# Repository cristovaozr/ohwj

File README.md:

# OHWJ - Open hardware Joystick

Open hardware joystick - OHWJ (pronounces Oh-Jay) - is the first project where I am attempting to build a hardware with basic firmware for the controller setup.

## CPU

The CPU is an STM32F030C6 microcontroller with the following hardware enabled

* LQFP48 48 pin, 32K FLASH and 4K of SRAM, 7mm x 7mm size;
* 48MHz with internal 8MHz oscillator external 8MHz XTAL;
* Full 16-bit input port for buttons with internal pull-up resistors enabled;
  * No additional hardware for buttons necessary! If LOW then button is pressed;
* Four 12bit ADC channels for analog inputs;
  * 1kHz default frequency sampling for the buttons and ADC provided by internal timer (TIM14);
* SPI Full-duplex SPI for data transfer;
* Dedicated ST-Link pins available for debugging and flashing purposes.

Optional stuff:
* USART
* I2C
* GPIO:
  * Up to 8 GPIO available if external XTAL is not available;
  * Up to 6 GPIO available if external XTAL is available.

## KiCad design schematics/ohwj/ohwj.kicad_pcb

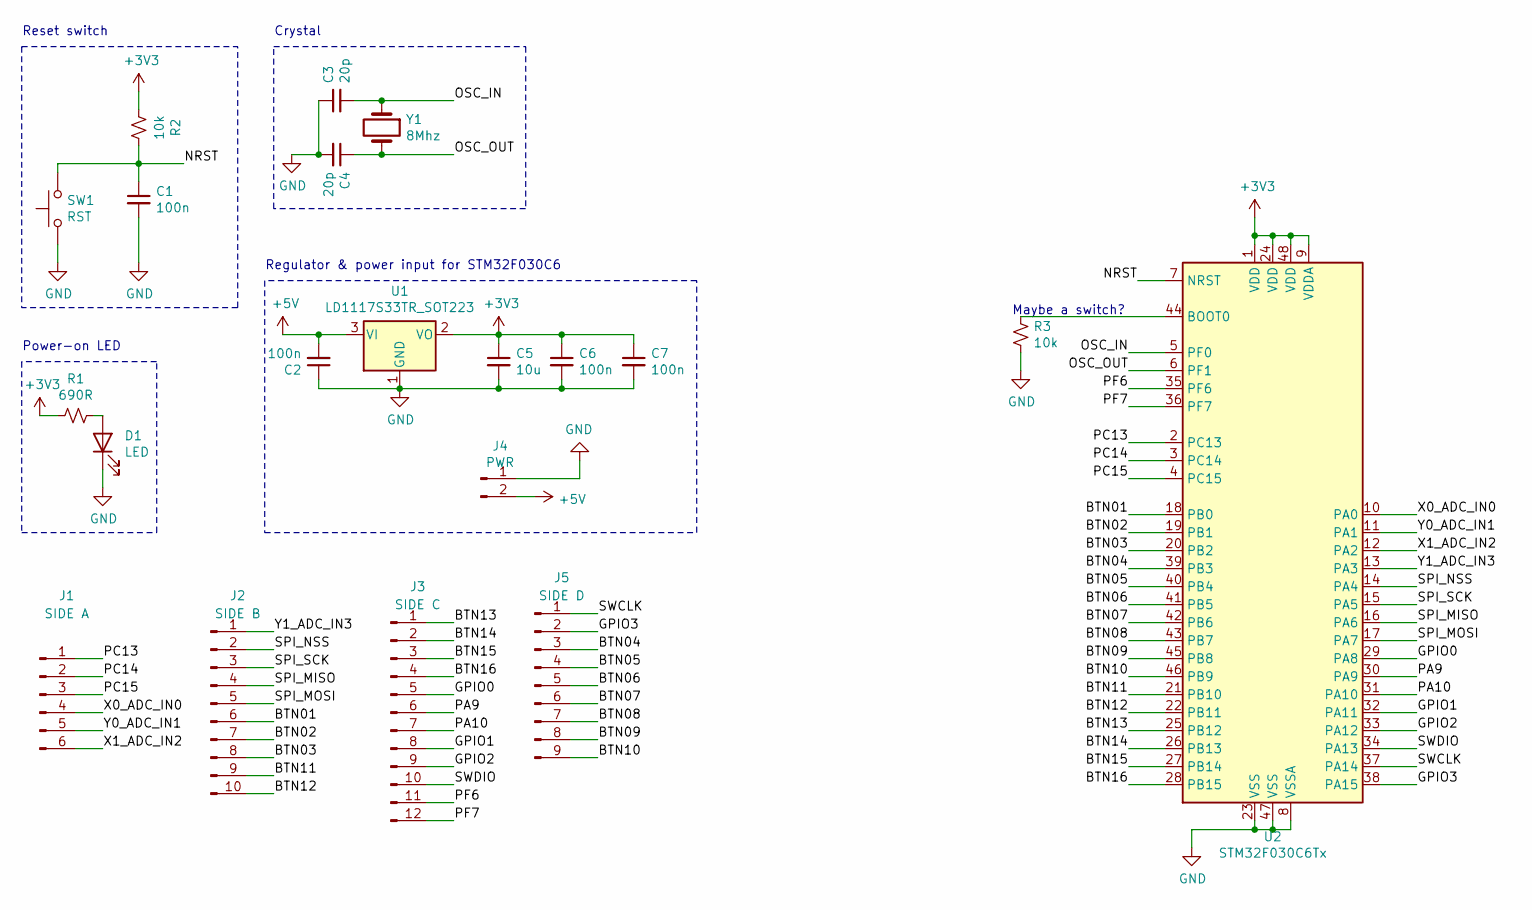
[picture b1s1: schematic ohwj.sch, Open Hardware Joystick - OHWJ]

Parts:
C1, C2, C6, C7: 100n; C_0603_1608Metric
C3, C4: 20p; C_0603_1608Metric
C5: 10u; C_0603_1608Metric
D1: LED; LED_0603_1608Metric
J1: SIDE A; PinHeader_1x06_P2.54mm_Vertical
J2: SIDE B; PinHeader_1x10_P2.54mm_Vertical
J3: SIDE C; PinHeader_1x12_P2.54mm_Vertical
J4: PWR; PinHeader_1x02_P2.54mm_Vertical
J5: SIDE D; PinHeader_1x09_P2.54mm_Vertical
R1: 690R; R_0603_1608Metric
R2, R3: 10k; R_0603_1608Metric
SW1: RST; SW_PUSH_6mm_H4.3mm
U1: LD1117S33TR_SOT223; SOT-223-3_TabPin2
U2: STM32F030C6Tx; LQFP-48_7x7mm_P0.5mm
Y1: 8Mhz; Crystal_HC49-4H_Vertical

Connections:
+3V3: C5.1, C6.1, C7.1, R1.1, R2.1, U1.2 (VO), U2.1 (VDD), U2.9 (VDDA), U2.24 (VDD), U2.48 (VDD)
+5V: C2.2, J4.2, U1.3 (VI)
/BTN01: J2.6, U2.18 (PB0)
/BTN02: J2.7, U2.19 (PB1)
/BTN03: J2.8, U2.20 (PB2)
/BTN04: J5.3, U2.39 (PB3)
/BTN05: J5.4, U2.40 (PB4)
/BTN06: J5.5, U2.41 (PB5)
/BTN07: J5.6, U2.42 (PB6)
/BTN08: J5.7, U2.43 (PB7)
/BTN09: J5.8, U2.45 (PB8)
/BTN10: J5.9, U2.46 (PB9)
/BTN11: J2.9, U2.21 (PB10)
/BTN12: J2.10, U2.22 (PB11)
/BTN13: J3.1, U2.25 (PB12)
/BTN14: J3.2, U2.26 (PB13)
/BTN15: J3.3, U2.27 (PB14)
/BTN16: J3.4, U2.28 (PB15)
/GPIO0: J3.5, U2.29 (PA8)
/GPIO1: J3.8, U2.32 (PA11)
/GPIO2: J3.9, U2.33 (PA12)
/GPIO3: J5.2, U2.38 (PA15)
/NRST: C1.1, R2.2, SW1.2, U2.7 (NRST)
/OSC_IN: C3.2, U2.5 (PF0), Y1.1
/OSC_OUT: C4.1, U2.6 (PF1), Y1.2
/PA9: J3.6, U2.30 (PA9)
/PA10: J3.7, U2.31 (PA10)
/PC13: J1.1, U2.2 (PC13)
/PC14: J1.2, U2.3 (PC14)
/PC15: J1.3, U2.4 (PC15)
/PF6: J3.11, U2.35 (PF6)
/PF7: J3.12, U2.36 (PF7)
/SPI_MISO: J2.4, U2.16 (PA6)
/SPI_MOSI: J2.5, U2.17 (PA7)
/SPI_NSS: J2.2, U2.14 (PA4)
/SPI_SCK: J2.3, U2.15 (PA5)
/SWCLK: J5.1, U2.37 (PA14)
/SWDIO: J3.10, U2.34 (PA13)
/X0_ADC_IN0: J1.4, U2.10 (PA0)
/X1_ADC_IN2: J1.6, U2.12 (PA2)
/Y0_ADC_IN1: J1.5, U2.11 (PA1)
/Y1_ADC_IN3: J2.1, U2.13 (PA3)
GND: C1.2, C2.1, C3.1, C4.2, C5.2, C6.2, C7.2, D1.1 (K), J4.1, R3.2, SW1.1, U1.1 (GND), U2.8 (VSSA), U2.23 (VSS), U2.47 (VSS)
unnamed: D1.2 (A), R1.2
unnamed: R3.1, U2.44 (BOOT0)

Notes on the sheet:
Reset switch
Maybe a switch?
Power-on LED
Crystal
Regulator & power input for STM32F030C6

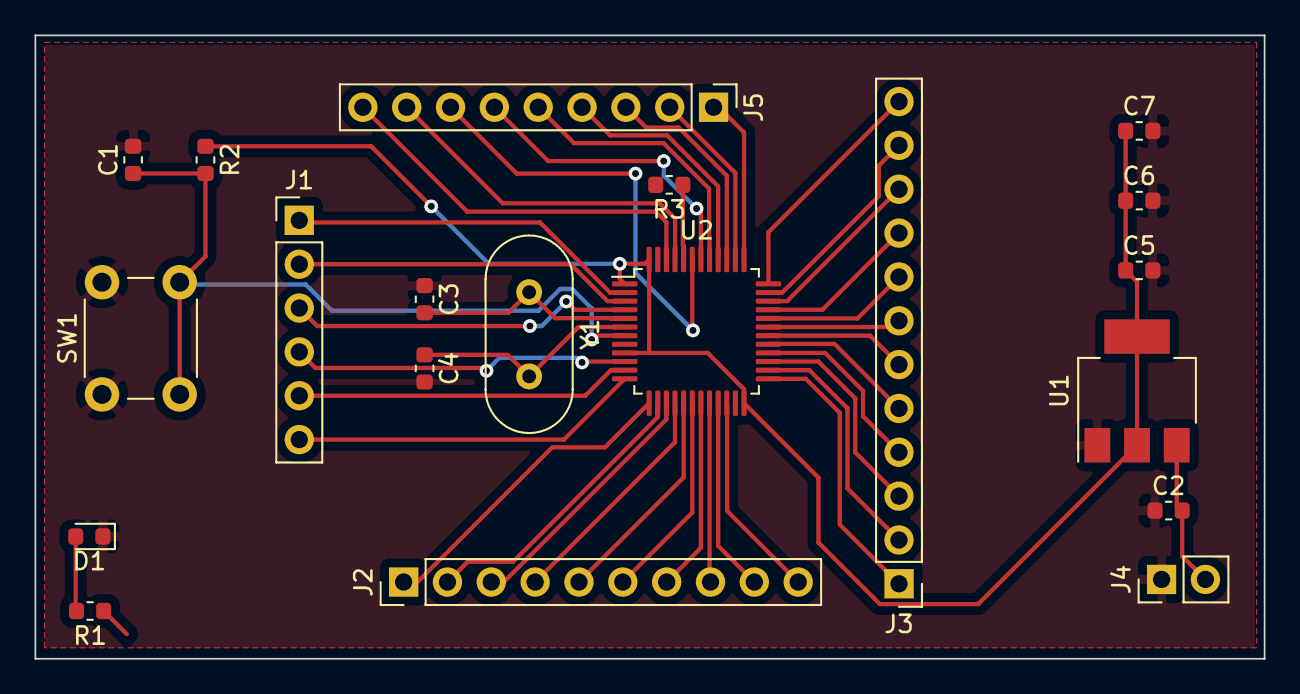
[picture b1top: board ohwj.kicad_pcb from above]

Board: 2 copper layers, 71.2 x 36.1 mm, 20 parts (0 on the bottom side), 45 nets.

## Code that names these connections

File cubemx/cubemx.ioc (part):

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Mcu.Name=STM32F030C6Tx
Mcu.Package=LQFP48
Mcu.UserName=STM32F030C6Tx
PA0.GPIOParameters=GPIO_Label
PA0.GPIO_Label=X0_ADC_IN0
PA0.Mode=IN0
PA0.Signal=ADC_IN0
PA1.GPIOParameters=GPIO_Label
PA1.GPIO_Label=Y0_ADC_IN1
PA1.Mode=IN1
PA1.Signal=ADC_IN1
PA10.Mode=Asynchronous
PA10.Signal=USART1_RX
PA13.Mode=Serial_Wire
PA13.Signal=SYS_SWDIO
PA14.Mode=Serial_Wire
PA14.Signal=SYS_SWCLK
PA2.GPIOParameters=GPIO_Label
PA2.GPIO_Label=X1_ADC_IN2
PA2.Mode=IN2
PA2.Signal=ADC_IN2
PA3.GPIOParameters=GPIO_Label
PA3.GPIO_Label=Y1_ADC_IN3
PA3.Mode=IN3
PA3.Signal=ADC_IN3
PA4.Mode=NSS_Signal_Hard_Input
PA4.Signal=SPI1_NSS
PA5.Mode=Full_Duplex_Slave
PA5.Signal=SPI1_SCK
PA6.Mode=Full_Duplex_Slave
PA6.Signal=SPI1_MISO
PA7.Mode=Full_Duplex_Slave
PA7.Signal=SPI1_MOSI
PA9.Mode=Asynchronous
PA9.Signal=USART1_TX
PB0.GPIOParameters=GPIO_PuPd
PB0.GPIO_PuPd=GPIO_PULLUP
PB0.Signal=GPIO_Input
PB1.GPIOParameters=GPIO_PuPd
PB1.GPIO_PuPd=GPIO_PULLUP
PB1.Signal=GPIO_Input
PB10.GPIOParameters=GPIO_PuPd
PB10.GPIO_PuPd=GPIO_PULLUP
PB10.Signal=GPIO_Input
PB11.GPIOParameters=GPIO_PuPd
PB11.GPIO_PuPd=GPIO_PULLUP
PB11.Signal=GPIO_Input
PB12.GPIOParameters=GPIO_PuPd
PB12.GPIO_PuPd=GPIO_PULLUP
PB12.Signal=GPIO_Input
PB13.GPIOParameters=GPIO_PuPd
PB13.GPIO_PuPd=GPIO_PULLUP
PB13.Signal=GPIO_Input
PB14.GPIOParameters=GPIO_PuPd
PB14.GPIO_PuPd=GPIO_PULLUP
PB14.Signal=GPIO_Input
PB15.GPIOParameters=GPIO_PuPd
PB15.GPIO_PuPd=GPIO_PULLUP
PB15.Signal=GPIO_Input
PB2.GPIOParameters=GPIO_PuPd
PB2.GPIO_PuPd=GPIO_PULLUP
PB2.Signal=GPIO_Input
PB3.GPIOParameters=GPIO_PuPd
PB3.GPIO_PuPd=GPIO_PULLUP
PB3.Signal=GPIO_Input
PB4.GPIOParameters=GPIO_PuPd
PB4.GPIO_PuPd=GPIO_PULLUP
PB4.Signal=GPIO_Input
PB5.GPIOParameters=GPIO_PuPd
PB5.GPIO_PuPd=GPIO_PULLUP
PB5.Signal=GPIO_Input
PB6.GPIOParameters=GPIO_PuPd
PB6.GPIO_PuPd=GPIO_PULLUP
PB6.Signal=GPIO_Input
PB7.GPIOParameters=GPIO_PuPd
PB7.GPIO_PuPd=GPIO_PULLUP
PB7.Signal=GPIO_Input
PB8.GPIOParameters=GPIO_PuPd
PB8.GPIO_PuPd=GPIO_PULLUP
PB8.Signal=GPIO_Input
PB9.GPIOParameters=GPIO_PuPd
PB9.GPIO_PuPd=GPIO_PULLUP
PB9.Signal=GPIO_Input
PF0-OSC_IN.Mode=HSE-External-Oscillator
PF0-OSC_IN.Signal=RCC_OSC_IN
PF1-OSC_OUT.Mode=HSE-External-Oscillator
PF1-OSC_OUT.Signal=RCC_OSC_OUT
PF6.Mode=I2C
PF6.Signal=I2C1_SCL
PF7.Mode=I2C
PF7.Signal=I2C1_SDA
RCC.SYSCLKFreq_VALUE=48000000
RCC.SYSCLKSource=RCC_SYSCLKSOURCE_PLLCLK
board=custom

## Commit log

2020-06-20 First commit with documentation
2020-06-20 Adding schematics with power, LED, RESET and BOOT0
2020-06-20 Update power and labels; placing labels for all pins
2020-06-21 Add 8MHz crystal; assing component to pins (reset missing)
2020-06-22 Add voltage regulator; defined all footprints
2020-06-26 Preliminar PCB layout
